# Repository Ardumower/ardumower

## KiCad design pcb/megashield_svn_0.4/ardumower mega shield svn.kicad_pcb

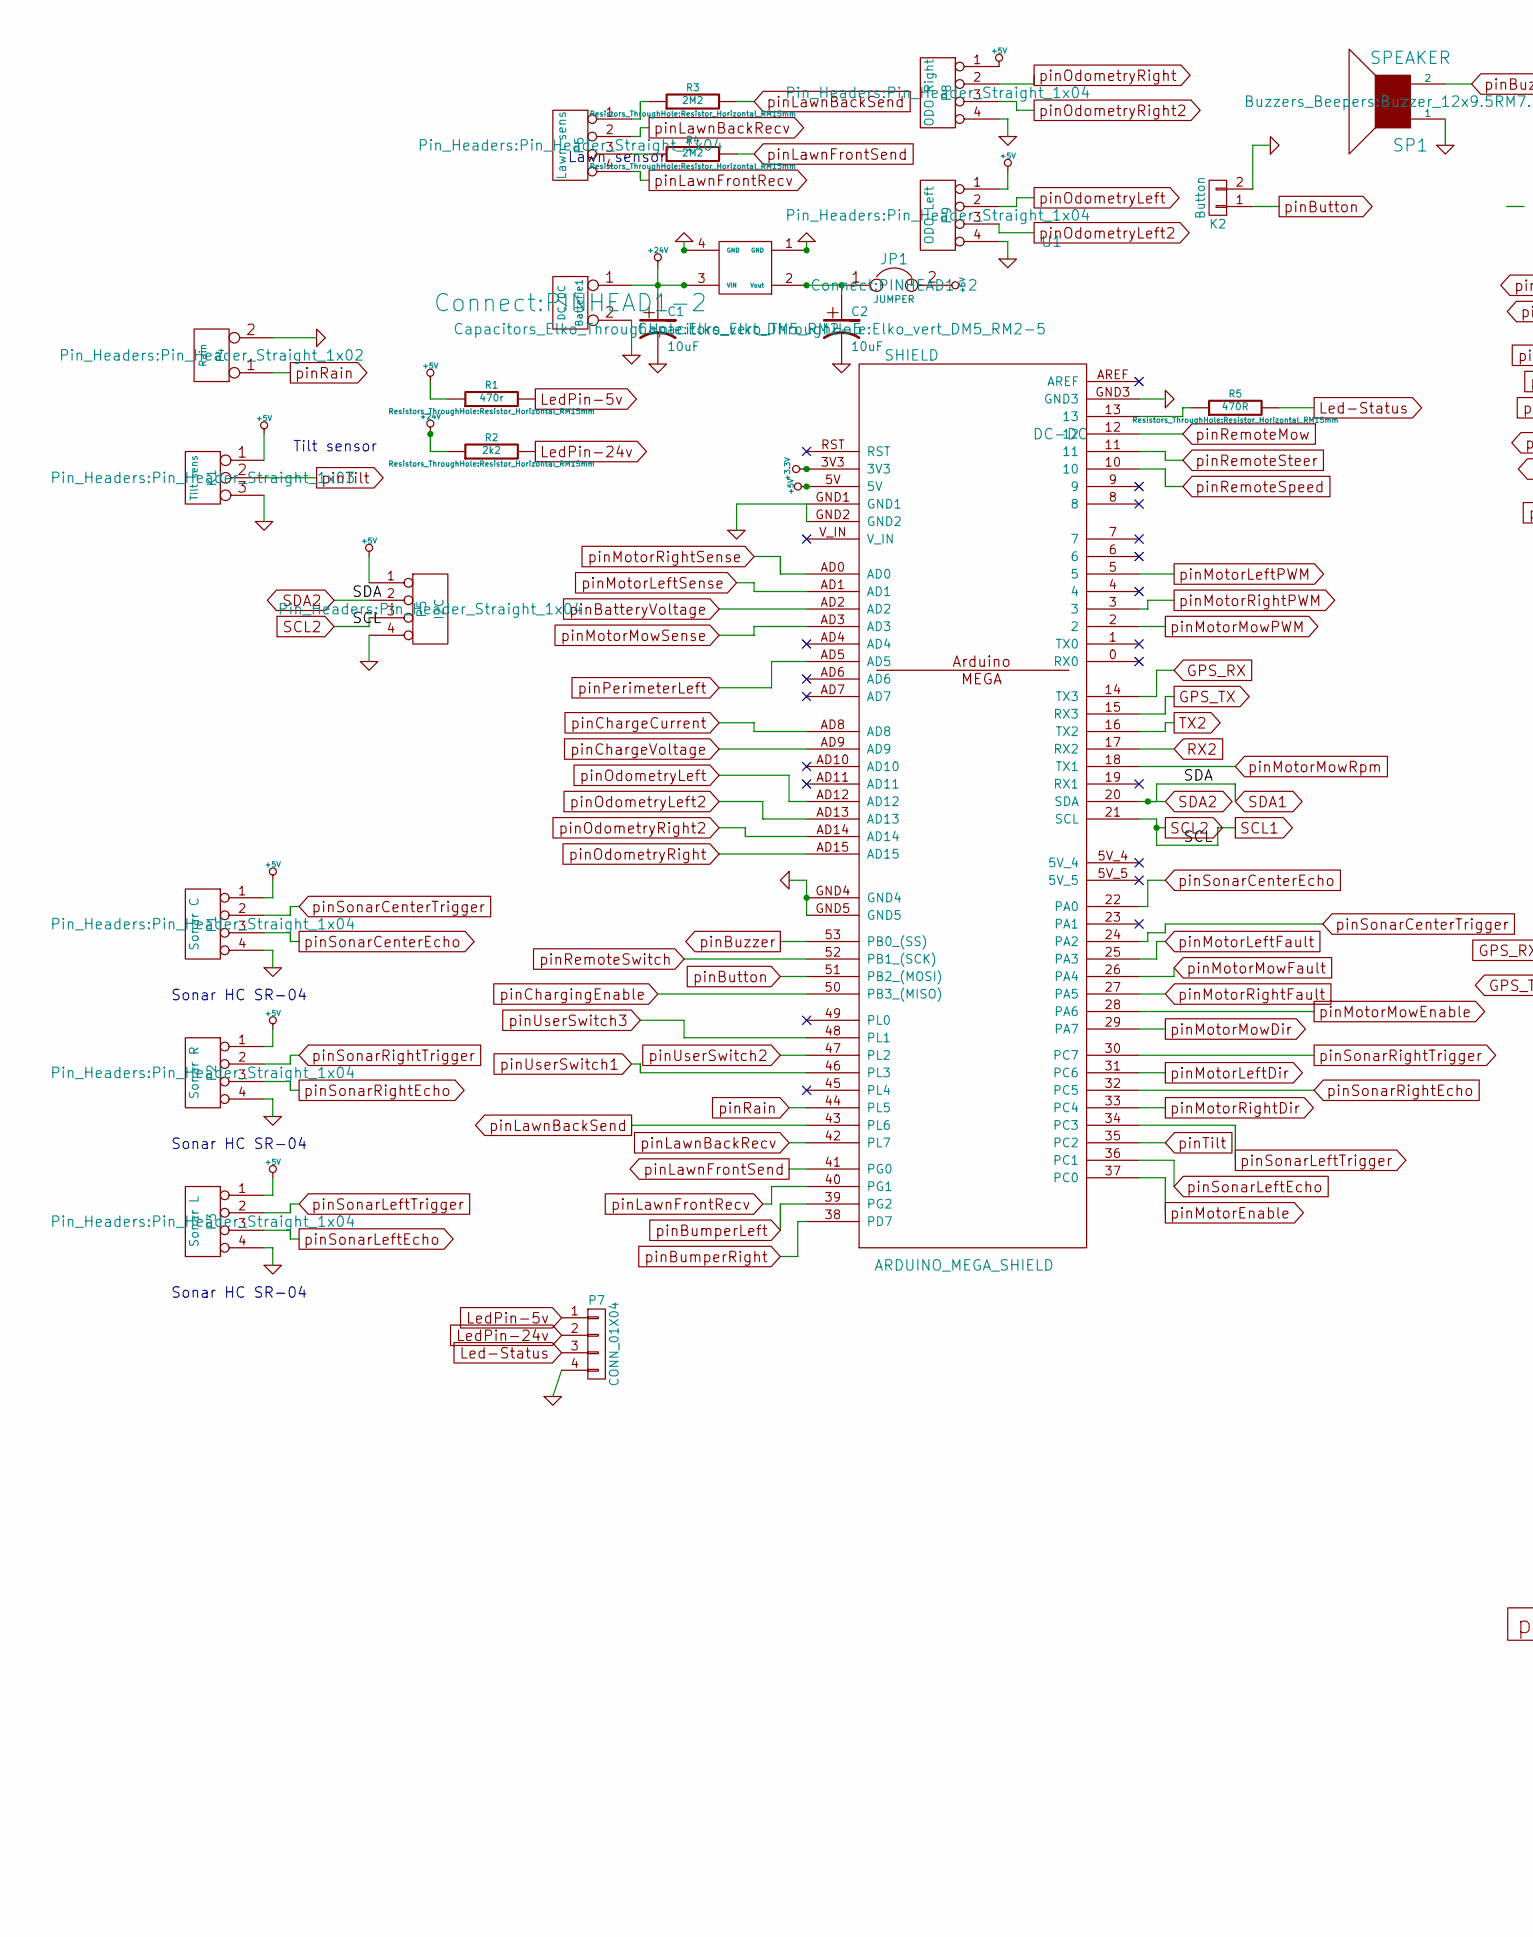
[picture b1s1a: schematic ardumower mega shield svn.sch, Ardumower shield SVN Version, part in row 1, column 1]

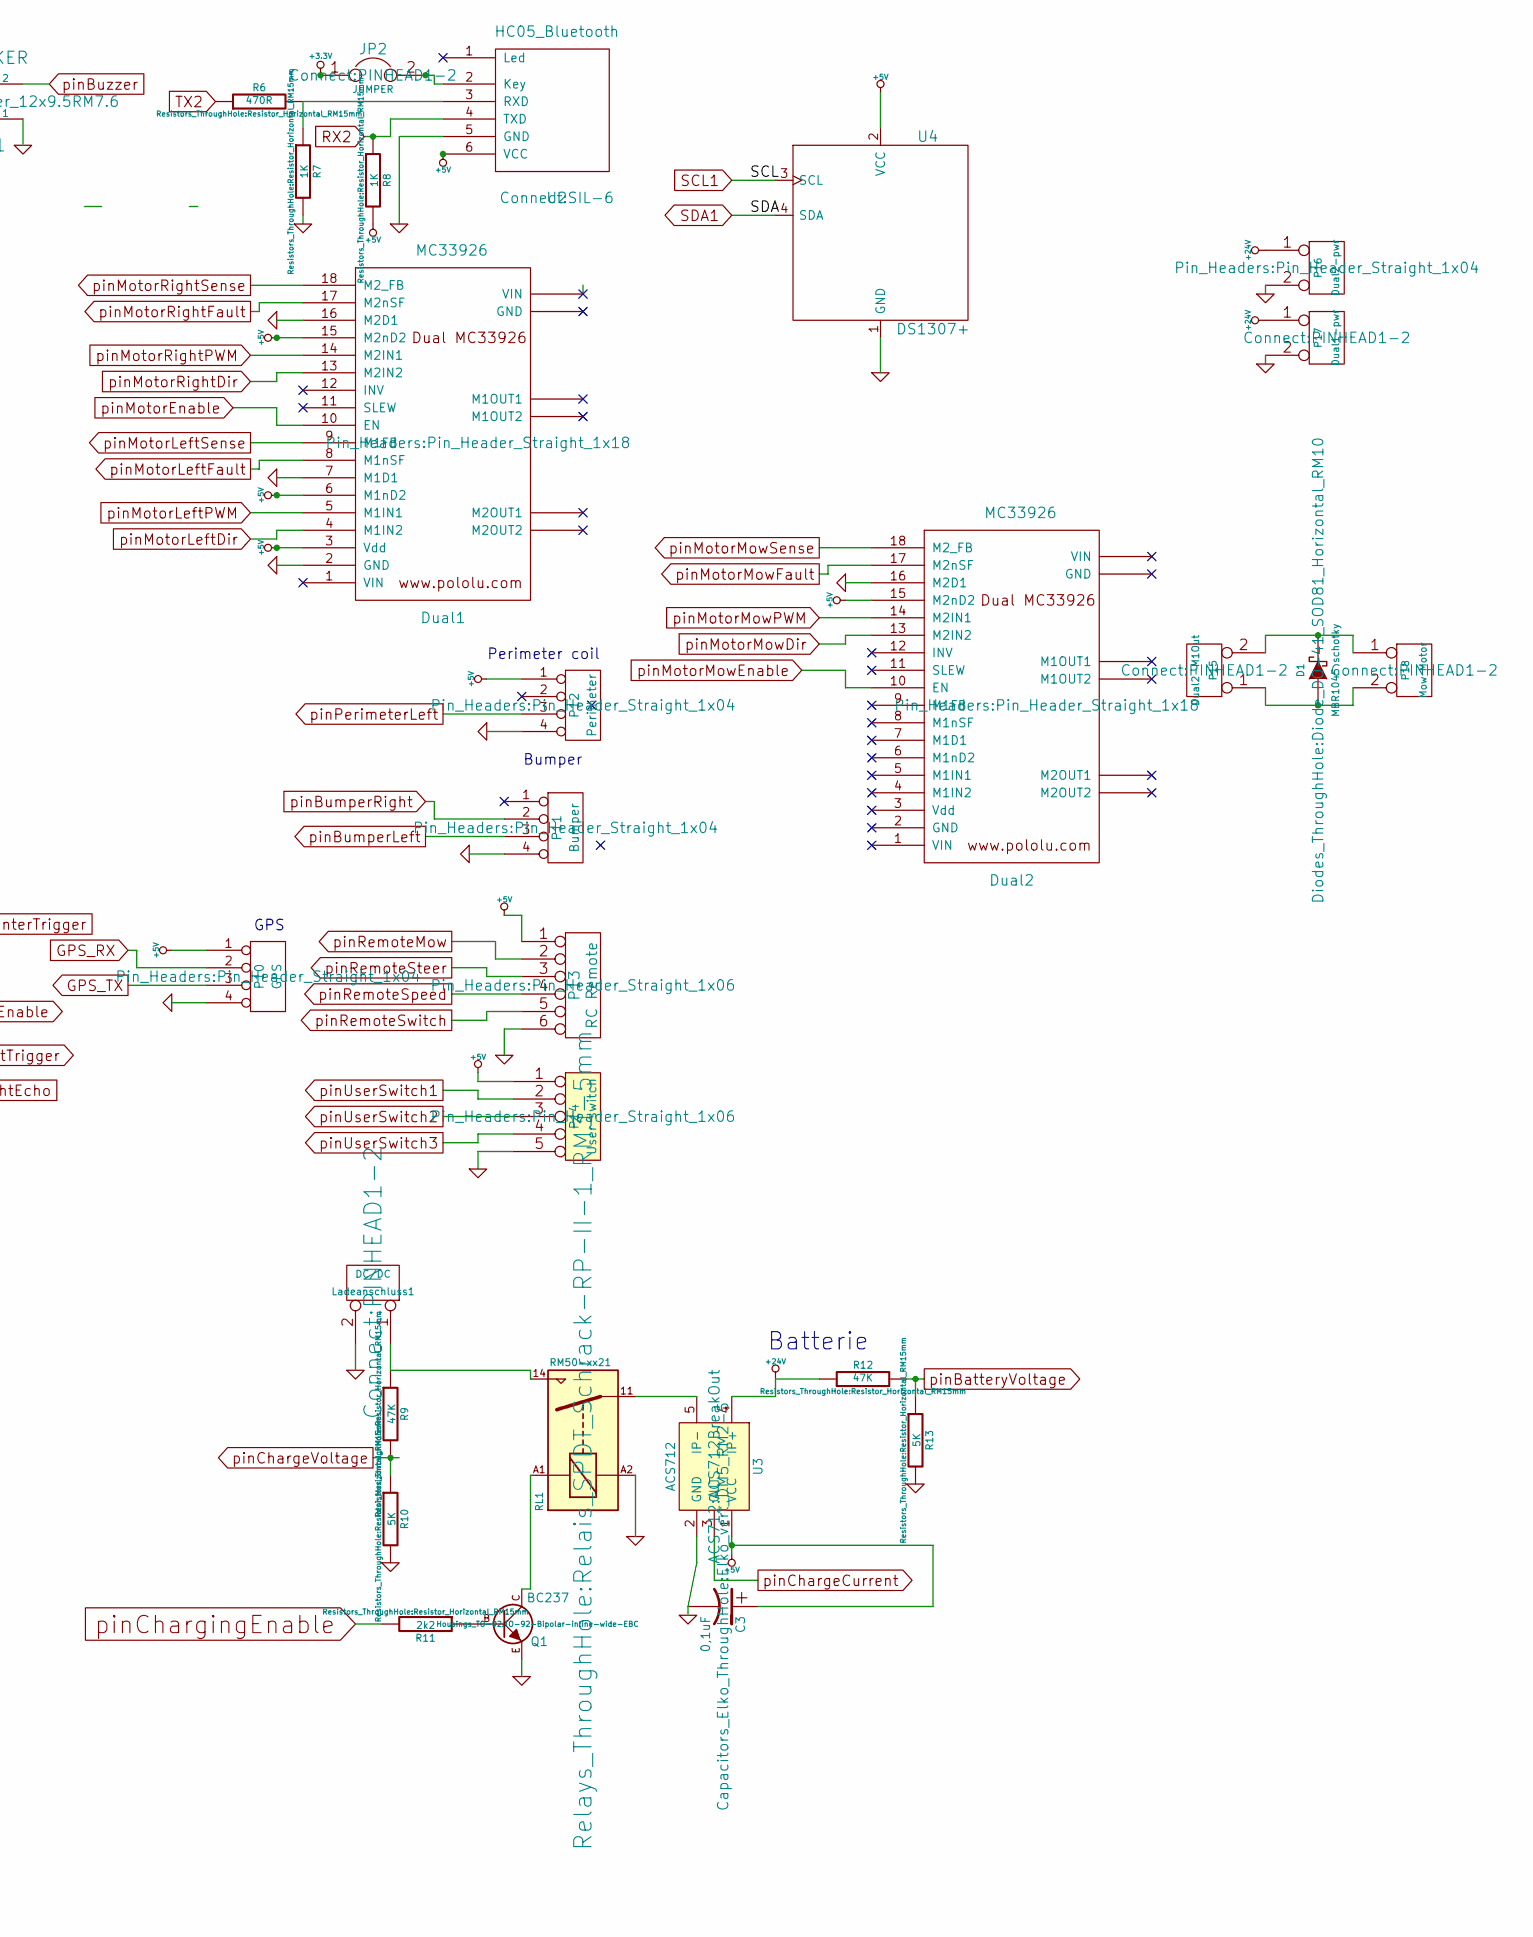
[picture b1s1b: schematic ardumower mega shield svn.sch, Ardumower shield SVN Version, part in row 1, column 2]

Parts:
Batterie1: DC/DC; PINHEAD1-2
C1, C2: 10uF; Elko_vert_DM5_RM2-5
C3: 0,1uF; Elko_vert_DM5_RM2-5
D1: MBR1045 schotky; Diode_DO-41_SOD81_Horizontal_RM10
Dual1, Dual2: MC33926; Pin_Header_Straight_1x18
JP1, JP2: JUMPER; PINHEAD1-2
K1: Tilt sens; Pin_Header_Straight_1x03
K2: Button; Pin_Header_Straight_1x02
Ladeanschluss1: DC/DC; PINHEAD1-2
P1: Sonar C; Pin_Header_Straight_1x04
P2: Sonar R; Pin_Header_Straight_1x04
P3: Sonar L; Pin_Header_Straight_1x04
P4: Rain; Pin_Header_Straight_1x02
P5: I2C; Pin_Header_Straight_1x04
P6: Lawn sens; Pin_Header_Straight_1x04
P7: CONN_01X04; Pin_Header_Straight_1x04
P8: ODO Right; Pin_Header_Straight_1x04
P9: ODO Left; Pin_Header_Straight_1x04
P10: GPS; Pin_Header_Straight_1x04
P11: Bumper; Pin_Header_Straight_1x04
P12: Perimeter; Pin_Header_Straight_1x04
P13: RC Remote; Pin_Header_Straight_1x06
P14: User switch; Pin_Header_Straight_1x06
P15: Dual2-M1Out; PINHEAD1-2
P16: Dual2-pwr; Pin_Header_Straight_1x04
P17: Dual1-pwr; PINHEAD1-2
P18: Mow Motor; PINHEAD1-2
Q1: BC237; TO-92-Bipolar-inline-wide-EBC
R1: 470r; Resistor_Horizontal_RM15mm
R2, R11: 2k2; Resistor_Horizontal_RM15mm
R3, R4: 2M2; Resistor_Horizontal_RM15mm
R5, R6: 470R; Resistor_Horizontal_RM15mm
R7, R8: 1K; Resistor_Horizontal_RM15mm
R9, R12: 47K; Resistor_Horizontal_RM15mm
R10, R13: 5K; Resistor_Horizontal_RM15mm
RL1: RM50-xx21; Relais_SPDT_Schrack-RP-II-1_RM3-5mm
SHIELD1: ARDUINO_MEGA_SHIELD; ARDUINO MEGA SHIELD
SP1: SPEAKER; Buzzer_12x9.5RM7.6
U1: DC-DC
U2: HC05_Bluetooth; SIL-6
U3: ACS712; ACS712BreakOut
U4: DS1307+; Pin_Header_Straight_1x04

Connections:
+3.3V: JP2.1, SHIELD1.3V3
+5V: C3.1, Dual1.3 (Vdd), Dual1.6 (M1nD2), Dual1.15 (M2nD2), Dual2.15 (M2nD2), JP1.2, K1.1, P1.1, P2.1, P3.1, P5.1, P8.1, P9.1, P10.1, P12.1, P13.1, P14.1, R1.1, R8.2, SHIELD1.5V, U2.6 (VCC), U3.1 (VCC), U4.2 (VCC)
+24V: Batterie1.1, C1.1, P16.1, P17.1, R2.1, R12.1, U1.3 (VIN), U3.4 (IP+)
GND: Batterie1.2 (PM), C1.2, C2.2, C3.2, Dual1.2 (GND), Dual1.7 (M1D1), Dual1.16 (M2D1), Dual2.16 (M2D1), K1.3, K2.2, Ladeanschluss1.2 (PM), P1.4, P2.4, P3.4, P4.2 (PM), P5.4, P7.4, P8.4, P9.4, P10.4, P11.4, P12.4, P13.6, P14.5, P16.2 (PM), P17.2 (PM), Q1.E, R7.2, R10.2, R13.2, RL1.A2, SHIELD1.GND1, SHIELD1.GND2, SHIELD1.GND3, SHIELD1.GND4, SHIELD1.GND5, SP1.1, U1.1 (GND), U1.4 (GND), U2.5 (GND), U3.2 (GND), U4.1 (GND)
GPS_RX: P10.2, SHIELD1.14 (TX3)
GPS_TX: P10.3, SHIELD1.15 (RX3)
Led-Status: P7.3, R5.2
LedPin-5v: P7.1, R1.2
LedPin-24v: P7.2, R2.2
unnamed: C2.1, JP1.1, U1.2 (Vout)
unnamed: D1.1 (A), P15.1, P18.2 (PM)
unnamed: D1.2 (K), P15.2 (PM), P18.1
unnamed: JP2.2, U2.2 (Key)
unnamed: Ladeanschluss1.1, R9.1, RL1.14
unnamed: P6.1, R3.1
unnamed: P6.3, R4.1
unnamed: Q1.B, R11.1
unnamed: Q1.C, RL1.A1
unnamed: R5.1, SHIELD1.13
unnamed: R6.2, R7.1, U2.3 (RXD)
unnamed: RL1.11, U3.5 (IP-)
RX2: R8.1, SHIELD1.17 (RX2), U2.4 (TXD)
SCL2: P5.3, SHIELD1.21 (SCL), U4.3 (SCL)
SDA2: P5.2, SHIELD1.20 (SDA), U4.4 (SDA)
TX2: R6.1, SHIELD1.16 (TX2)
pinBatteryVoltage: R12.2, R13.1, SHIELD1.AD2
pinBumperLeft: P11.3, SHIELD1.39 (PG2)
pinBumperRight: P11.2, SHIELD1.38 (PD7)
pinButton: K2.1, SHIELD1.51 (PB2_(MOSI))
pinBuzzer: SHIELD1.53 (PB0_(SS)), SP1.2
pinChargeCurrent: SHIELD1.AD8, U3.3 (OUT)
pinChargeVoltage: R9.2, R10.1, SHIELD1.AD9
pinChargingEnable: R11.2, SHIELD1.50 (PB3_(MISO))
pinLawnBackRecv: P6.2, SHIELD1.42 (PL7)
pinLawnBackSend: R3.2, SHIELD1.43 (PL6)
pinLawnFrontRecv: P6.4, SHIELD1.40 (PG1)
pinLawnFrontSend: R4.2, SHIELD1.41 (PG0)
pinMotorEnable: Dual1.10 (EN), SHIELD1.37 (PC0)
pinMotorLeftDir: Dual1.4 (M1IN2), SHIELD1.31 (PC6)
pinMotorLeftFault: Dual1.8 (M1nSF), SHIELD1.25 (PA3)
pinMotorLeftPWM: Dual1.5 (M1IN1), SHIELD1.5
pinMotorLeftSense: Dual1.9 (M1FB), SHIELD1.AD1
pinMotorMowDir: Dual2.13 (M2IN2), SHIELD1.29 (PA7)
pinMotorMowEnable: Dual2.10 (EN), SHIELD1.28 (PA6)
pinMotorMowFault: Dual2.17 (M2nSF), SHIELD1.26 (PA4)
pinMotorMowPWM: Dual2.14 (M2IN1), SHIELD1.2
pinMotorMowRpm: SHIELD1.18 (TX1)
pinMotorMowSense: Dual2.18 (M2_FB), SHIELD1.AD3
pinMotorRightDir: Dual1.13 (M2IN2), SHIELD1.33 (PC4)
pinMotorRightFault: Dual1.17 (M2nSF), SHIELD1.27 (PA5)
pinMotorRightPWM: Dual1.14 (M2IN1), SHIELD1.3
pinMotorRightSense: Dual1.18 (M2_FB), SHIELD1.AD0
pinOdometryLeft: P9.2, SHIELD1.AD12
pinOdometryLeft2: P9.3, SHIELD1.AD13
pinOdometryRight: P8.2, SHIELD1.AD15
pinOdometryRight2: P8.3, SHIELD1.AD14
pinPerimeterLeft: P12.3, SHIELD1.AD5
pinRain: P4.1, SHIELD1.44 (PL5)
pinRemoteMow: P13.2, SHIELD1.12
pinRemoteSpeed: P13.4, SHIELD1.10
pinRemoteSteer: P13.3, SHIELD1.11
pinRemoteSwitch: P13.5, SHIELD1.52 (PB1_(SCK))
pinSonarCenterEcho: P1.3, SHIELD1.22 (PA0)
pinSonarCenterTrigger: P1.2, SHIELD1.24 (PA2)
pinSonarLeftEcho: P3.3, SHIELD1.36 (PC1)
pinSonarLeftTrigger: P3.2, SHIELD1.34 (PC3)
pinSonarRightEcho: P2.3, SHIELD1.32 (PC5)
pinSonarRightTrigger: P2.2, SHIELD1.30 (PC7)
pinTilt: K1.2 (PM), SHIELD1.35 (PC2)
pinUserSwitch1: P14.2, SHIELD1.46 (PL3)
pinUserSwitch2: P14.3, SHIELD1.47 (PL2)
pinUserSwitch3: P14.4, SHIELD1.48 (PL1)

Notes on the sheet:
Sonar HC SR-04
Perimeter coil
Lawn sensor
Tilt sensor
GPS
Bumper
Batterie

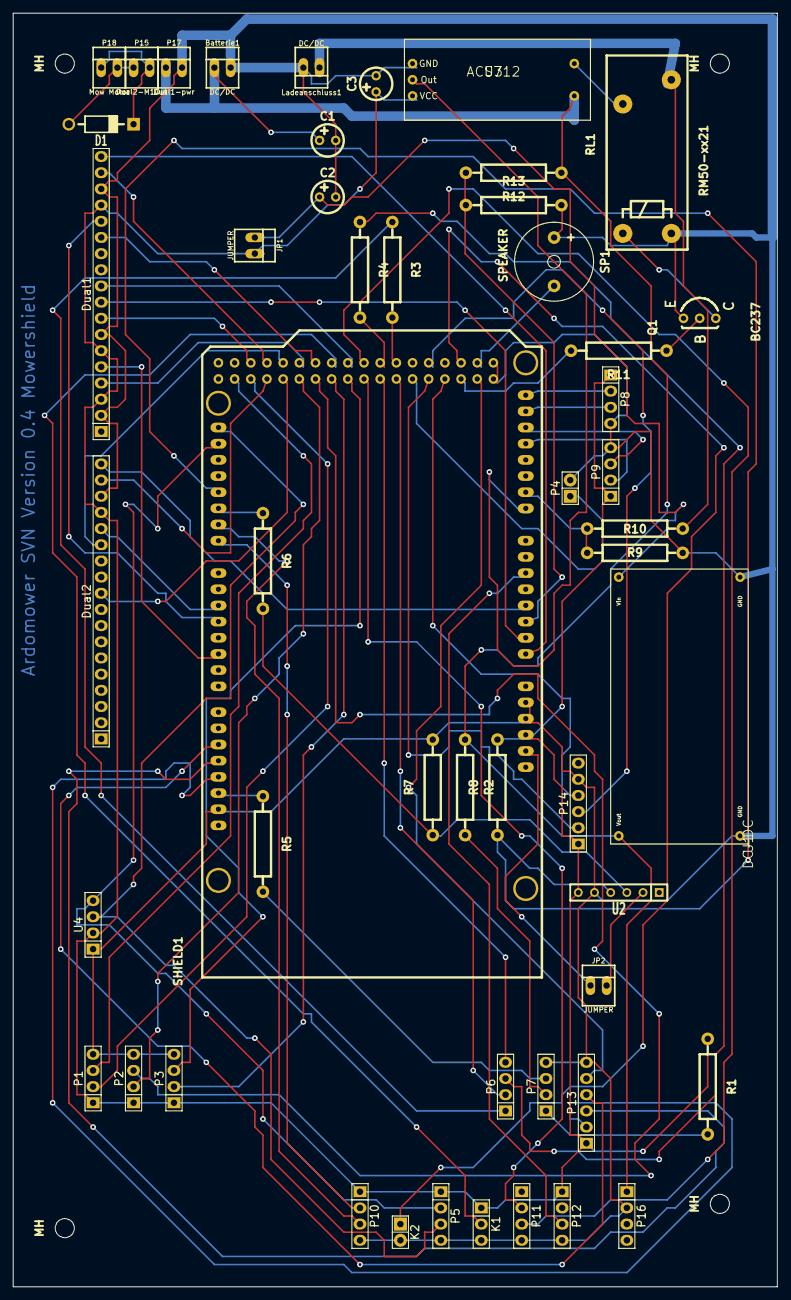
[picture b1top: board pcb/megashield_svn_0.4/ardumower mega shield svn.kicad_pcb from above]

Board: 2 copper layers, 120.0 x 200.0 mm, 55 parts (0 on the bottom side), 71 nets.

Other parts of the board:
MH: MountingHole_3mm_RevA_Date21Jun2010; MountingHole_3mm
MH#2, MH#3, MH#4: MountingHole_3mm_RevA_Date21Jun2010; MountingHole_3mm

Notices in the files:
pcb/megashield_v1/ardumower mega shield V1.00.kicad_pcb:
(C) 2014 RFsolution
parts and their libraries:
Released under the Creative Commons Attribution Share-Alike 3.0 License
